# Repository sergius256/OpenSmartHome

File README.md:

# OpenSmartHome

OpenSmartHome is a hardware project aimed to develop a set of modules
capable to bind mechanical and electrical parts of house engineering
systems with known software smart house systems such as OpenHAB via
simple protocol.

# Changes

2016-05-11.

	* L298 moved to other side of the board in window-blind PCB.

	* ISP header changed to 6-pin and moved to other side of the
          PCB in window-blind.

	* Firmware for window-blind reflects changes in PCB.

2016-05-05.

	* Removed sprintf() calls to optimize memory usage.

	* Number of parser calls per rxbuffer was limited to 1 for the
          moment.

	* First version of window blind firmware written.

	* Firmware binary generated for AtMega48PA.

2016-05-02.

	* Added RS-485 shield for Raspberry Pi.

	* Added parser library to bring command recognition
          functionality to device firmwares.

	* Added window blind driver PCB layout.

	* Added PDF versions of PCB layouts and schematics for all
          hardware.

2016-04-24.

	Added window blind drive controller schematics.

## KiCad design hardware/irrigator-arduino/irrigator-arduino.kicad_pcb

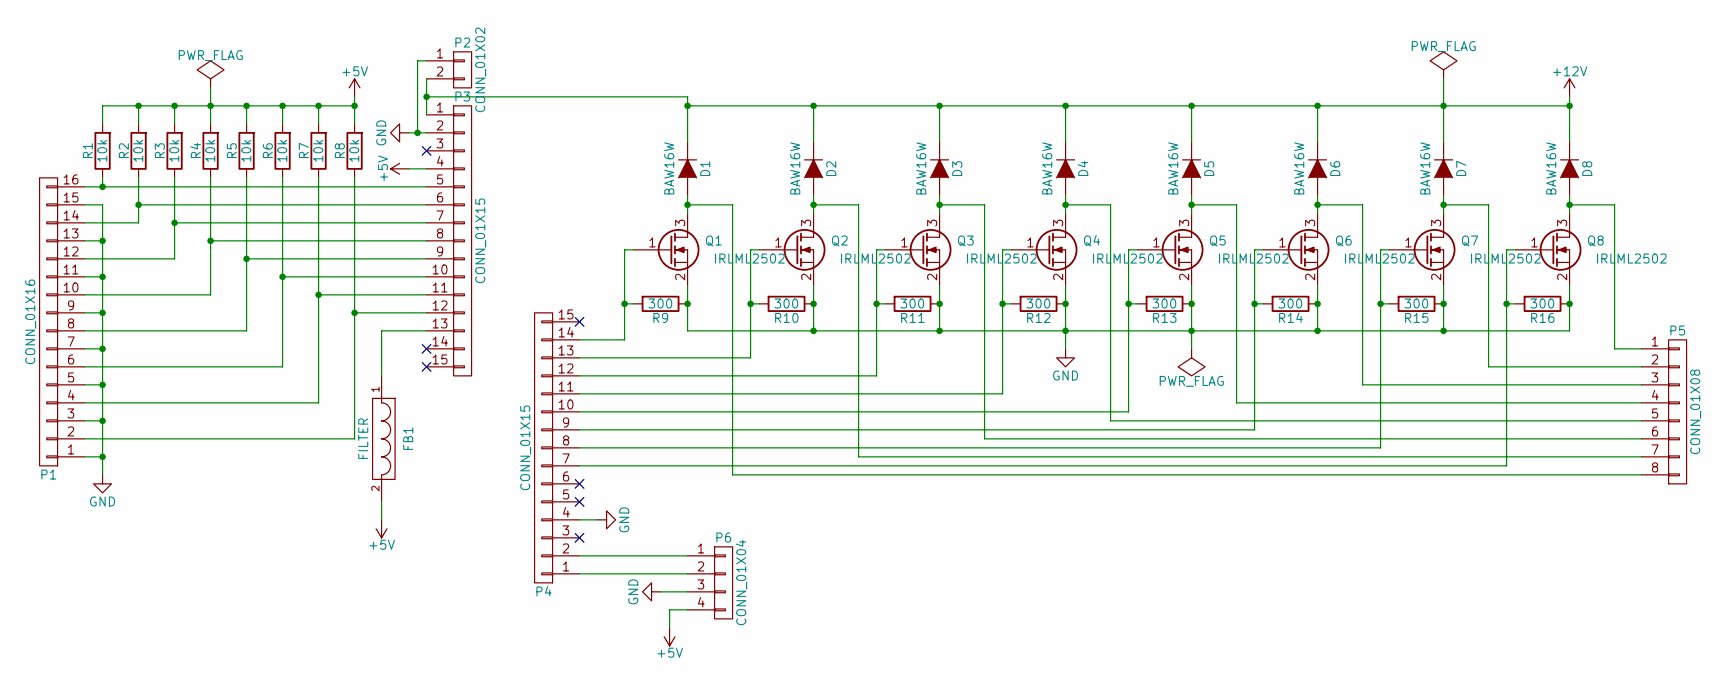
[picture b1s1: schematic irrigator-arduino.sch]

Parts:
D1, D2, D3, D4, D5, D6, D7, D8: BAW16W; D_SOD-123
FB1: FILTER; R_Axial_Power_L25.0mm_W9.0mm_P30.48mm
P1: CONN_01X16; Pin_Header_Straight_1x16_Pitch2.54mm
P2: CONN_01X02; Pin_Header_Straight_1x02_Pitch2.54mm
P3, P4: CONN_01X15; Pin_Header_Straight_1x15_Pitch2.54mm
P5: CONN_01X08; Pin_Header_Straight_1x08_Pitch2.54mm
P6: CONN_01X04; Pin_Header_Angled_1x04_Pitch2.54mm
Q1, Q2, Q3, Q4, Q5, Q6, Q7, Q8: IRLML2502; SOT-23_Handsoldering
R1, R2, R3, R4, R5, R6, R7, R8: 10k; R_1206_HandSoldering
R9, R10, R11, R12, R13, R14, R15, R16: 300; R_1206_HandSoldering

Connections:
+5V: FB1.2, P3.4, P6.4, R1.2, R2.2, R3.2, R4.2, R5.2, R6.2, R7.2, R8.2
+12V: D1.1 (K), D2.1 (K), D3.1 (K), D4.1 (K), D5.1 (K), D6.1 (K), D7.1 (K), D8.1 (K), P2.2, P3.1
GND: P1.1, P1.3, P1.5, P1.7, P1.9, P1.11, P1.13, P1.15, P2.1, P3.2, P4.4, P6.3, Q1.2 (S), Q2.2 (S), Q3.2 (S), Q4.2 (S), Q5.2 (S), Q6.2 (S), Q7.2 (S), Q8.2 (S), R9.1, R10.1, R11.1, R12.1, R13.1, R14.1, R15.1, R16.1
unnamed: D1.2 (A), P5.8, Q1.3 (D)
unnamed: D2.2 (A), P5.7, Q2.3 (D)
unnamed: D3.2 (A), P5.6, Q3.3 (D)
unnamed: D4.2 (A), P5.5, Q4.3 (D)
unnamed: D5.2 (A), P5.4, Q5.3 (D)
unnamed: D6.2 (A), P5.3, Q6.3 (D)
unnamed: D7.2 (A), P5.2, Q7.3 (D)
unnamed: D8.2 (A), P5.1, Q8.3 (D)
unnamed: FB1.1, P3.13
unnamed: P1.2, P3.12, R8.1
unnamed: P1.4, P3.11, R7.1
unnamed: P1.6, P3.10, R6.1
unnamed: P1.8, P3.9, R5.1
unnamed: P1.10, P3.8, R4.1
unnamed: P1.12, P3.7, R3.1
unnamed: P1.14, P3.6, R2.1
unnamed: P1.16, P3.5, R1.1
unnamed: P4.1, P6.2
unnamed: P4.2, P6.1
unnamed: P4.7, Q8.1 (G), R16.2
unnamed: P4.8, Q7.1 (G), R15.2
unnamed: P4.9, Q6.1 (G), R14.2
unnamed: P4.10, Q5.1 (G), R13.2
unnamed: P4.11, Q4.1 (G), R12.2
unnamed: P4.12, Q3.1 (G), R11.2
unnamed: P4.13, Q2.1 (G), R10.2
unnamed: P4.14, Q1.1 (G), R9.2

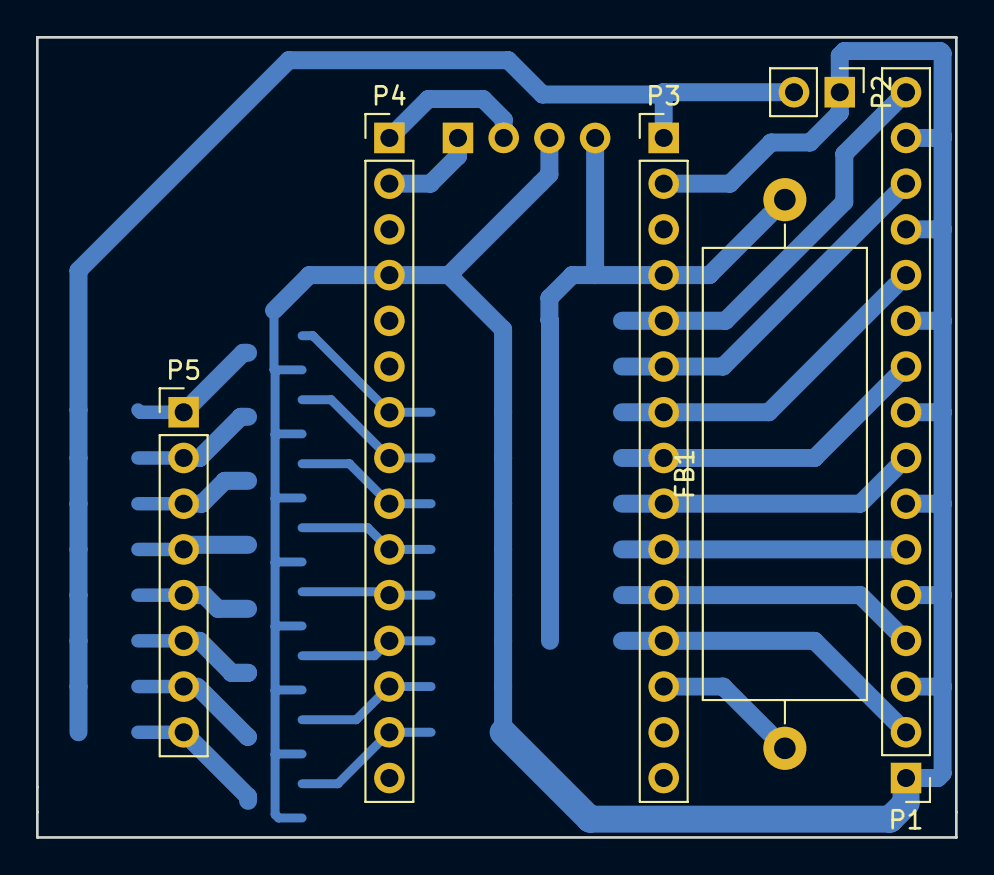
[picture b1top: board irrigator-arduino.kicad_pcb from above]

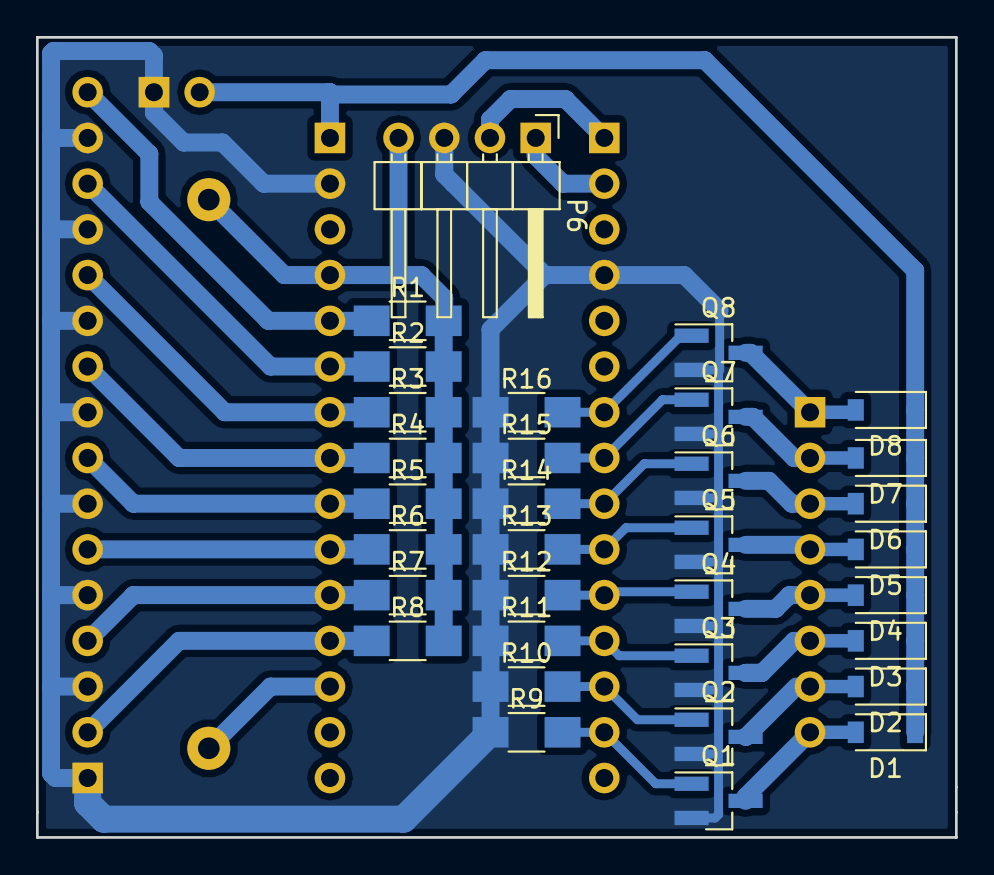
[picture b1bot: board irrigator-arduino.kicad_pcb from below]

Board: 2 copper layers, 51.1 x 44.4 mm, 39 parts (33 on the bottom side), 30 nets.

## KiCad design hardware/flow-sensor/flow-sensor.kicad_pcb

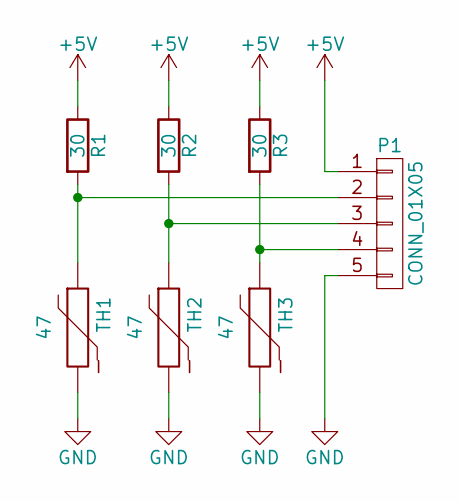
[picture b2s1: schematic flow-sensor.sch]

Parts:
P1: CONN_01X05; Pin_Header_Straight_1x05_Pitch2.54mm
R1, R2, R3: 30; R_1206_HandSoldering
TH1, TH2, TH3: 47; R_0805_HandSoldering

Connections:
+5V: P1.1, R1.1, R2.1, R3.1
GND: P1.5, TH1.2, TH2.2, TH3.2
unnamed: P1.2, R1.2, TH1.1
unnamed: P1.3, R2.2, TH2.1
unnamed: P1.4, R3.2, TH3.1

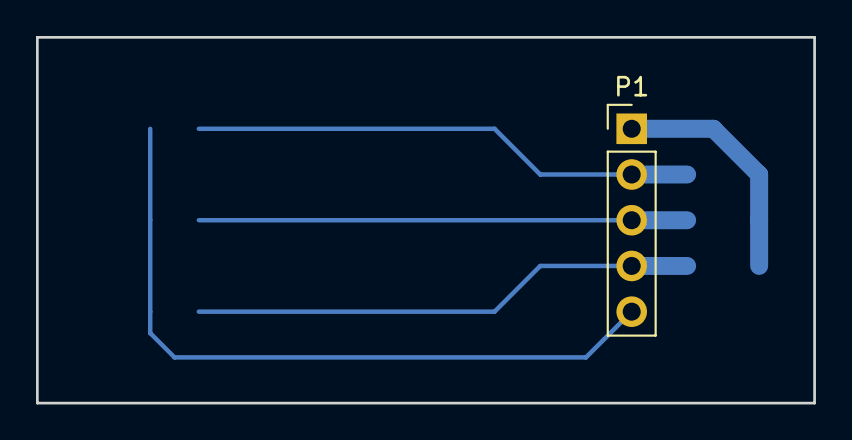
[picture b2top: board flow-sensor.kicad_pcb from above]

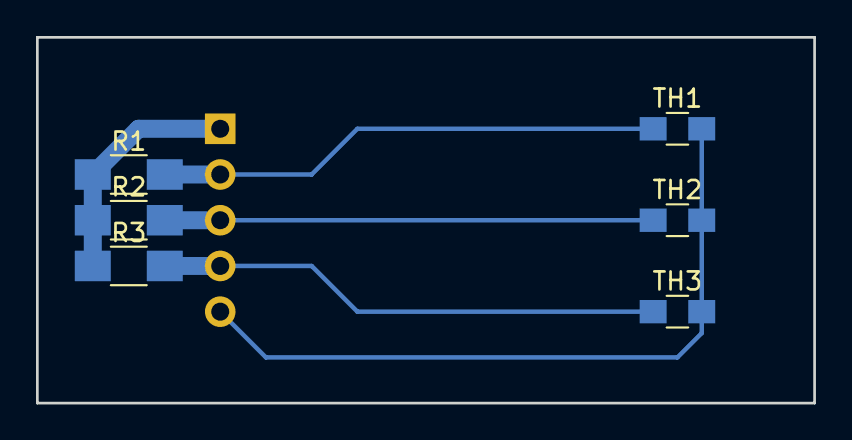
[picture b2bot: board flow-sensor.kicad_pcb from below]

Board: 2 copper layers, 43.2 x 20.3 mm, 7 parts (6 on the bottom side), 5 nets.

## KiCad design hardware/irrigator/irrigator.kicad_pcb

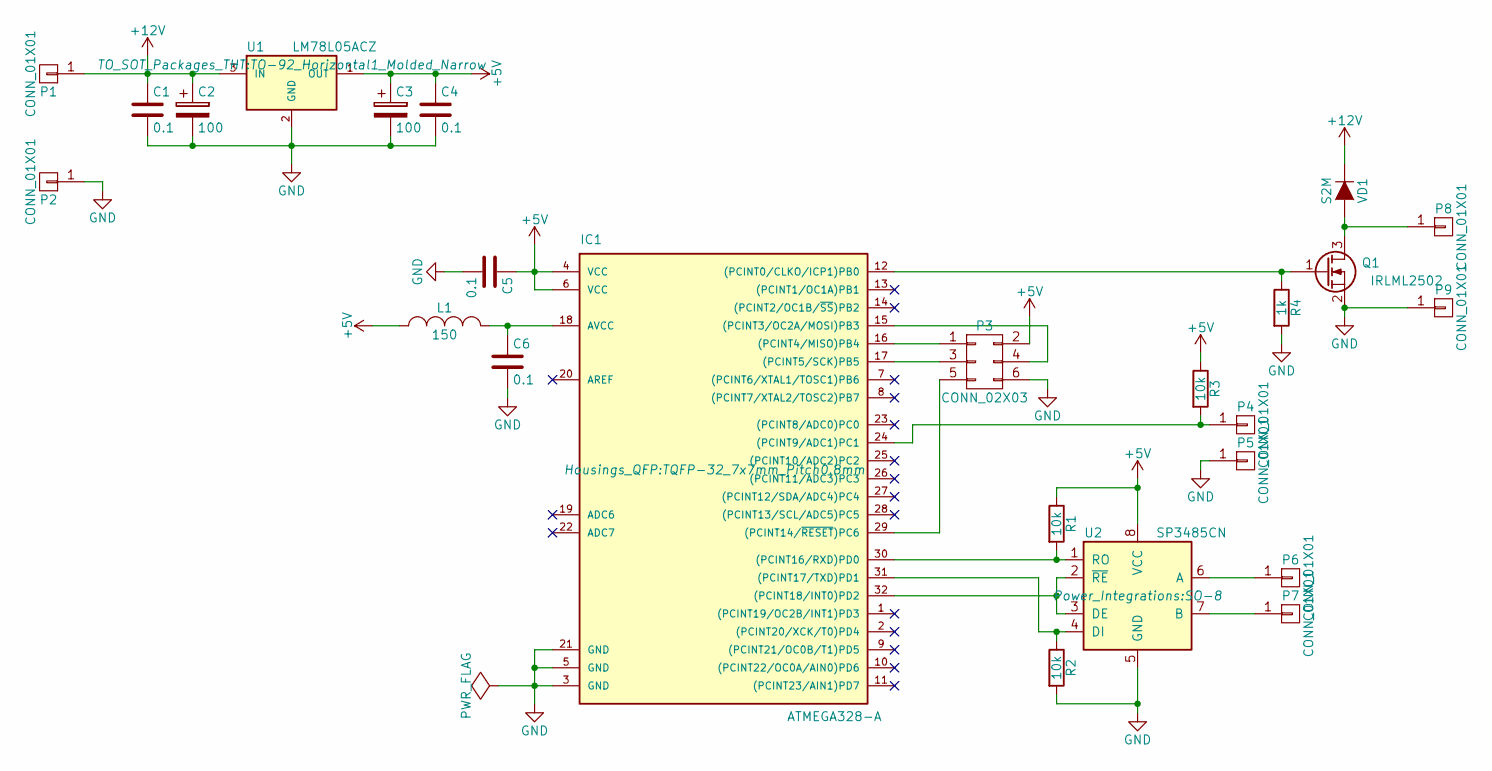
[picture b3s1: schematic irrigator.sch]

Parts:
C1, C4, C5, C6: 0.1; C_1206_HandSoldering
C2, C3: 100; TantalC_SizeD_EIA-7343_HandSoldering
IC1: ATMEGA328-A; TQFP-32_7x7mm_Pitch0.8mm
L1: 150; Choke_Horizontal_RM25mm
P1, P2, P4, P5, P6, P7, P8, P9: CONN_01X01; 1pin
P3: CONN_02X03; Pin_Header_Straight_2x03
Q1: IRLML2502; SOT-23_Handsoldering
R1, R2, R3: 10k; R_1206_HandSoldering
R4: 1k; R_1206_HandSoldering
U1: LM78L05ACZ; TO-92_Horizontal1_Molded_Narrow
U2: SP3485CN; SO-8
VD1: S2M; SMB_Handsoldering

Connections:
+5V: C3.1, C4.1, C5.1, IC1.4 (VCC), IC1.6 (VCC), L1.1, P3.2, R1.1, R3.1, U1.1 (OUT), U2.8 (VCC)
+12V: C1.1, C2.1, P1.1, U1.3 (IN), VD1.1 (K)
GND: C1.2, C2.2, C3.2, C4.2, C5.2, C6.2, IC1.3 (GND), IC1.5 (GND), IC1.21 (GND), P2.1, P3.6, P5.1, P9.1, Q1.2 (S), R2.2, R4.2, U1.2 (GND), U2.5 (GND)
unnamed: C6.1, IC1.18 (AVCC), L1.2
unnamed: IC1.12 ((PCINT0/CLKO/ICP1)PB0), Q1.1 (G), R4.1
unnamed: IC1.15 ((PCINT3/OC2A/MOSI)PB3), P3.4
unnamed: IC1.16 ((PCINT4/MISO)PB4), P3.1
unnamed: IC1.17 ((PCINT5/SCK)PB5), P3.3
unnamed: IC1.24 ((PCINT9/ADC1)PC1), P4.1, R3.2
unnamed: IC1.29 ((PCINT14/~RESET~)PC6), P3.5
unnamed: IC1.30 ((PCINT16/RXD)PD0), R1.2, U2.1 (RO)
unnamed: IC1.31 ((PCINT17/TXD)PD1), R2.1, U2.4 (DI)
unnamed: IC1.32 ((PCINT18/INT0)PD2), U2.2 (~RE~), U2.3 (DE)
unnamed: P6.1, U2.6 (A)
unnamed: P7.1, U2.7 (B)
unnamed: P8.1, Q1.3 (D), VD1.2 (A)

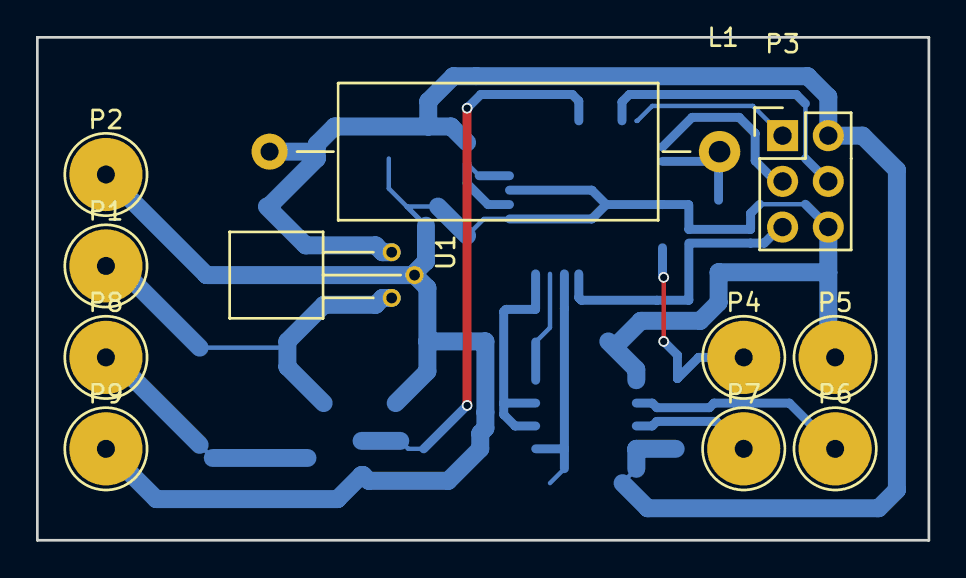
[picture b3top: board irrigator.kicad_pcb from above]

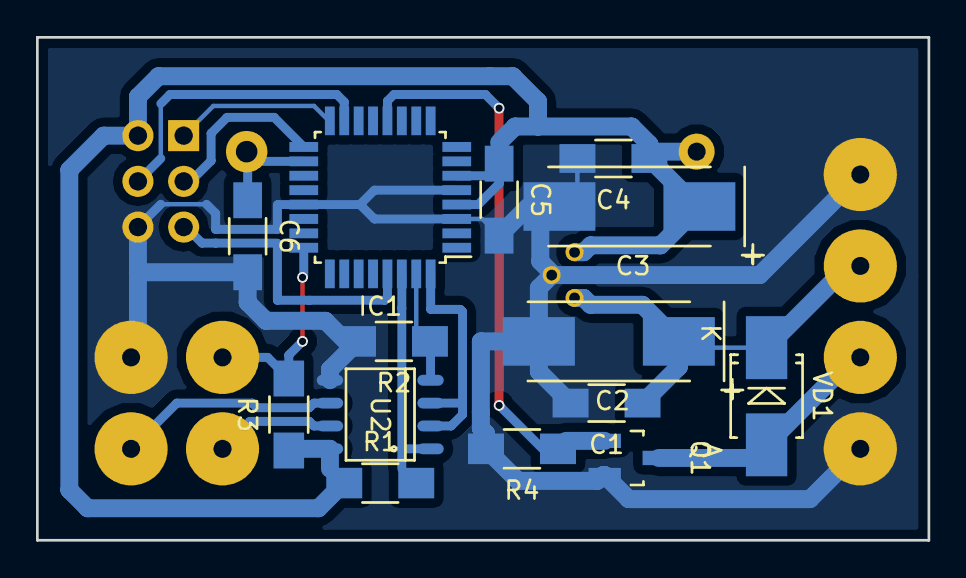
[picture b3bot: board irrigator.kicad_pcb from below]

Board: 2 copper layers, 49.5 x 27.9 mm, 25 parts (14 on the bottom side), 16 nets.

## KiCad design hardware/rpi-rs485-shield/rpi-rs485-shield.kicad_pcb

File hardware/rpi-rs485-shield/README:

OpenSmartHome RS-485 shield for Raspberry Pi copyright (C) 2016
Sergey Portnov (sergius256@gmail.com)

This schematic and printed circuit board design are released under the
terms of Creative Commons license v4.0, Attribution-ShareAlike. Author
holds no responsibility for any damage caused by the usage of this
materials.

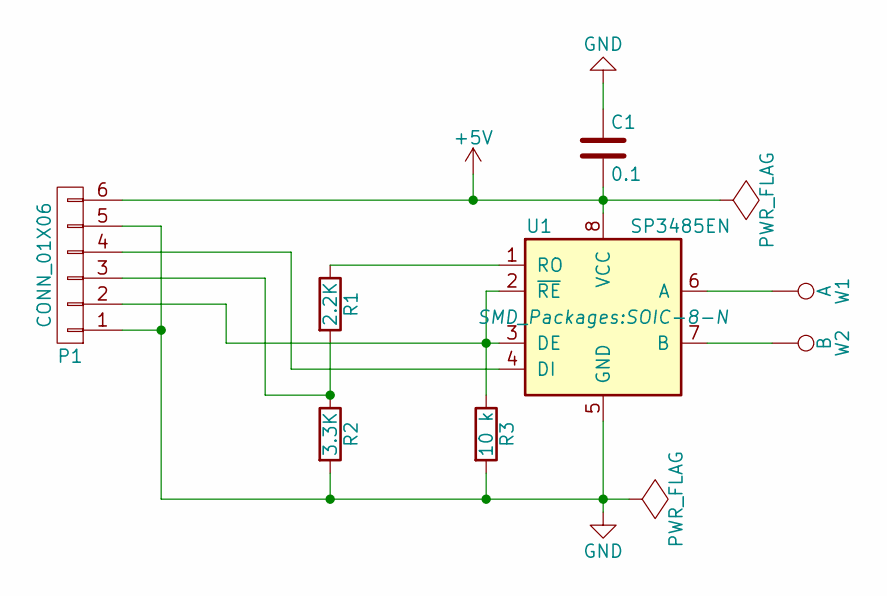
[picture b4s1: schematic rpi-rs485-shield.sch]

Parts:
C1: 0.1; C_1206_HandSoldering
P1: CONN_01X06; Pin_Header_Straight_1x06
R1: 2.2K; R_1206_HandSoldering
R2: 3.3K; R_1206_HandSoldering
R3: 10 k; R_1206_HandSoldering
U1: SP3485EN; SOIC-8-N
W1: A; SolderWirePad_single_1mmDrill
W2: B; SolderWirePad_single_1mmDrill

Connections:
+5V: C1.2, P1.6, U1.8 (VCC)
GND: C1.1, P1.1, P1.5, R2.2, R3.2, U1.5 (GND)
unnamed: P1.2, R3.1, U1.2 (~RE~), U1.3 (DE)
unnamed: P1.3, R1.2, R2.1
unnamed: P1.4, U1.4 (DI)
unnamed: R1.1, U1.1 (RO)
unnamed: U1.6 (A), W1.1
unnamed: U1.7 (B), W2.1

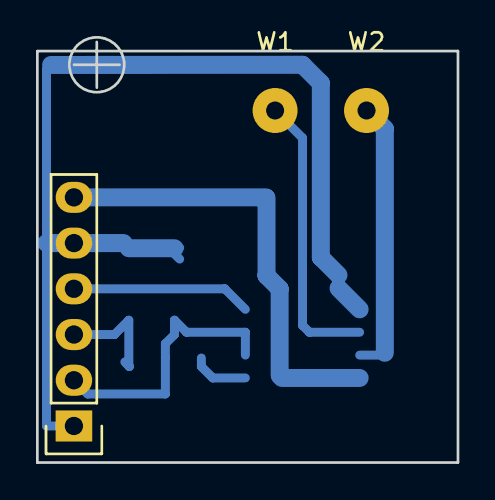
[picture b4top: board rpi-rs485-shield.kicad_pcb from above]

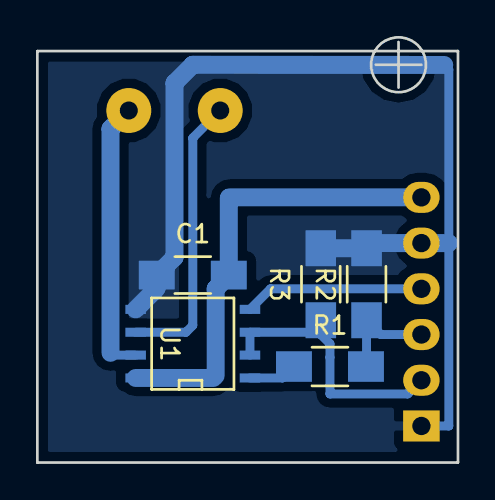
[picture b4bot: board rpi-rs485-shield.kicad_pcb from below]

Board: 2 copper layers, 23.4 x 23.6 mm, 8 parts (5 on the bottom side), 8 nets.

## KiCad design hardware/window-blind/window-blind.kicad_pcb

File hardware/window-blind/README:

OpenSmartHome window blind drive copyright (C) 2014-2016
Sergey Portnov (sergius256@gmail.com),
Raed Romanov (raid_r@mail.ru),
Anatoly Karavaev (karavaevas@gmail.com),
Evgeny Kaner (kanerea@xakep.ru)

This schematic and printed circuit board design are released under the
terms of Creative Commons license v4.0, Attribution-ShareAlike.

Schematics use Kicad Library by W. Lain - kcswalter@member.fsf.org.

Authors holds no responsibility for any damage caused by the usage of
this materials.

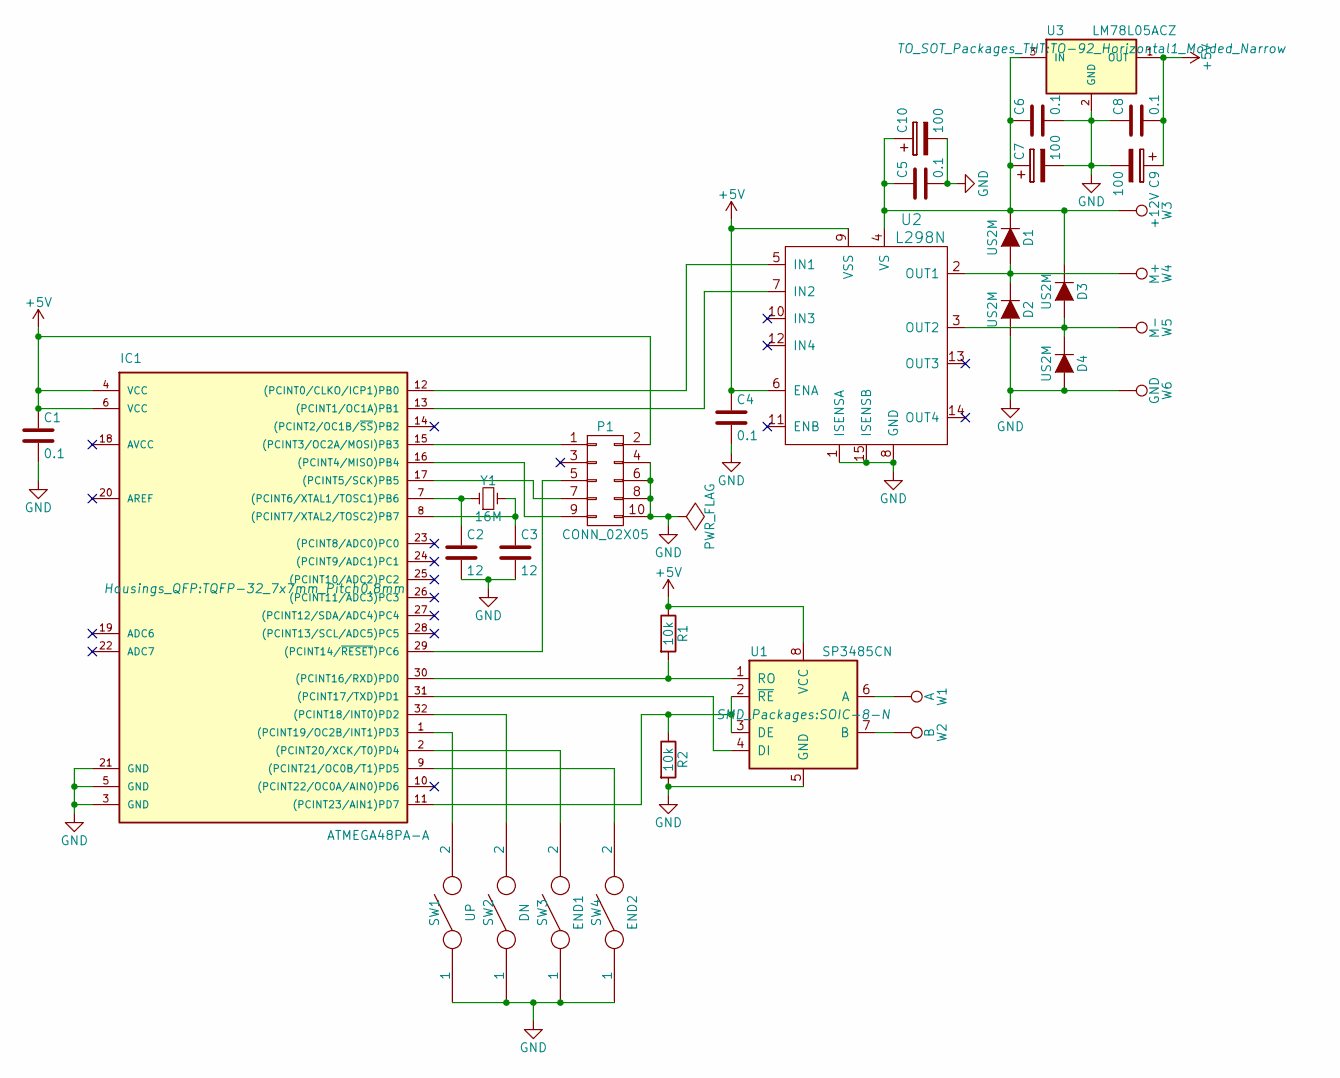
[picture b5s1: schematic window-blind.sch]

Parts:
C1, C4, C5, C6, C8: 0.1; C_1206_HandSoldering
C2, C3: 12; C_1206_HandSoldering
C7, C9, C10: 100; TantalC_SizeD_EIA-7343_HandSoldering
D1, D2, D3, D4: US2M; DO-214AB_Handsoldering
IC1: ATMEGA48PA-A; TQFP-32_7x7mm_Pitch0.8mm
P1: CONN_02X05; Pin_Header_Straight_2x05
R1, R2: 10k; R_1206_HandSoldering
SW1: UP; SW_SPST_B3S-1000
SW2: DN; SW_SPST_B3S-1000
SW3: END1; Resistor_Horizontal_RM15mm
SW4: END2; Resistor_Horizontal_RM15mm
U1: SP3485CN; SOIC-8-N
U2: L298N; Multiwatt_15_Vertical
U3: LM78L05ACZ; TO-92_Horizontal1_Molded_Narrow
W1: A; SolderWirePad_single_1mmDrill
W2: B; SolderWirePad_single_1mmDrill
W3: +12V; SolderWirePad_single_1mmDrill
W4: M+; SolderWirePad_single_1mmDrill
W5: M-; SolderWirePad_single_1mmDrill
W6: GND; SolderWirePad_single_1mmDrill
Y1: 16M; Crystal_HC49-SD_SMD

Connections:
+5V: C1.1, C4.1, C8.2, C9.1, IC1.4 (VCC), IC1.6 (VCC), P1.2, R1.1, U1.8 (VCC), U2.6 (ENA), U2.9 (VSS), U3.1 (OUT)
GND: C1.2, C2.2, C3.2, C4.2, C5.2, C6.2, C7.2, C8.1, C9.2, C10.2, D2.2 (A), D4.2 (A), IC1.3 (GND), IC1.5 (GND), IC1.21 (GND), P1.4, P1.6, P1.8, P1.10, R2.2, SW1.1, SW2.1, SW3.1, SW4.1, U1.5 (GND), U2.1 (ISENSA), U2.8 (GND), U2.15 (ISENSB), U3.2 (GND), W6.1
unnamed: C2.1, IC1.7 ((PCINT6/XTAL1/TOSC1)PB6), Y1.1
unnamed: C3.1, IC1.8 ((PCINT7/XTAL2/TOSC2)PB7), Y1.2
unnamed: C5.1, C6.1, C7.1, C10.1, D1.1 (K), D3.1 (K), U2.4 (VS), U3.3 (IN), W3.1
unnamed: D1.2 (A), D2.1 (K), U2.2 (OUT1), W4.1
unnamed: D3.2 (A), D4.1 (K), U2.3 (OUT2), W5.1
unnamed: IC1.1 ((PCINT19/OC2B/INT1)PD3), SW1.2
unnamed: IC1.2 ((PCINT20/XCK/T0)PD4), SW3.2
unnamed: IC1.9 ((PCINT21/OC0B/T1)PD5), SW4.2
unnamed: IC1.11 ((PCINT23/AIN1)PD7), R2.1, U1.2 (~RE~), U1.3 (DE)
unnamed: IC1.12 ((PCINT0/CLKO/ICP1)PB0), U2.5 (IN1)
unnamed: IC1.13 ((PCINT1/OC1A)PB1), U2.7 (IN2)
unnamed: IC1.15 ((PCINT3/OC2A/MOSI)PB3), P1.1
unnamed: IC1.16 ((PCINT4/MISO)PB4), P1.9
unnamed: IC1.17 ((PCINT5/SCK)PB5), P1.7
unnamed: IC1.29 ((PCINT14/~RESET~)PC6), P1.5
unnamed: IC1.30 ((PCINT16/RXD)PD0), R1.2, U1.1 (RO)
unnamed: IC1.31 ((PCINT17/TXD)PD1), U1.4 (DI)
unnamed: IC1.32 ((PCINT18/INT0)PD2), SW2.2
unnamed: U1.6 (A), W1.1
unnamed: U1.7 (B), W2.1

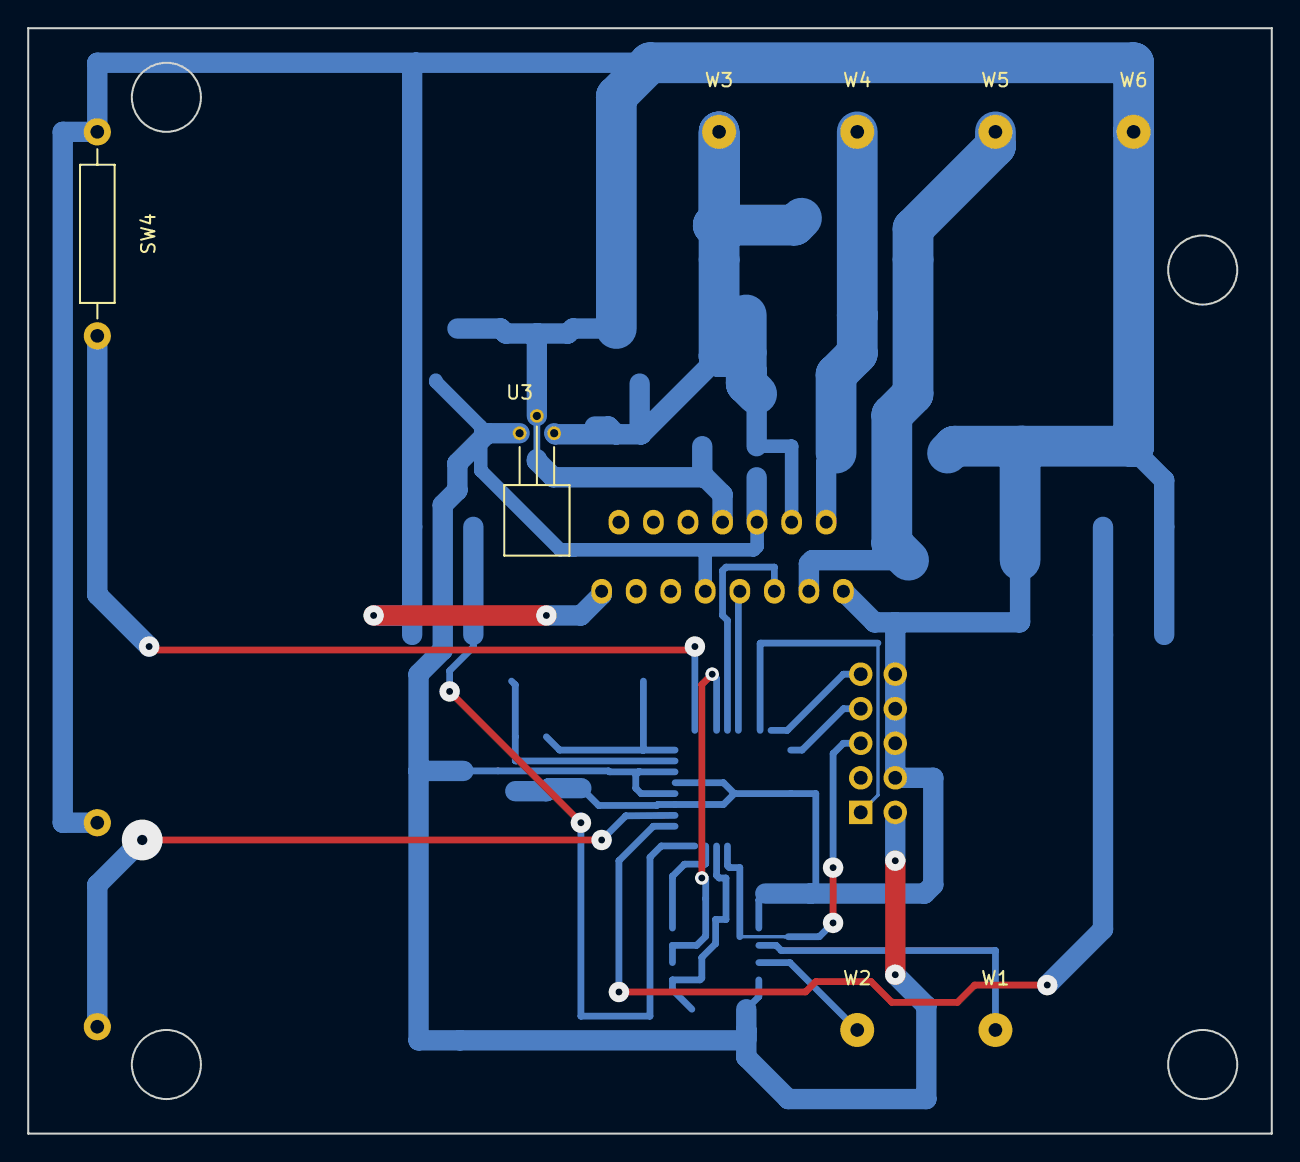
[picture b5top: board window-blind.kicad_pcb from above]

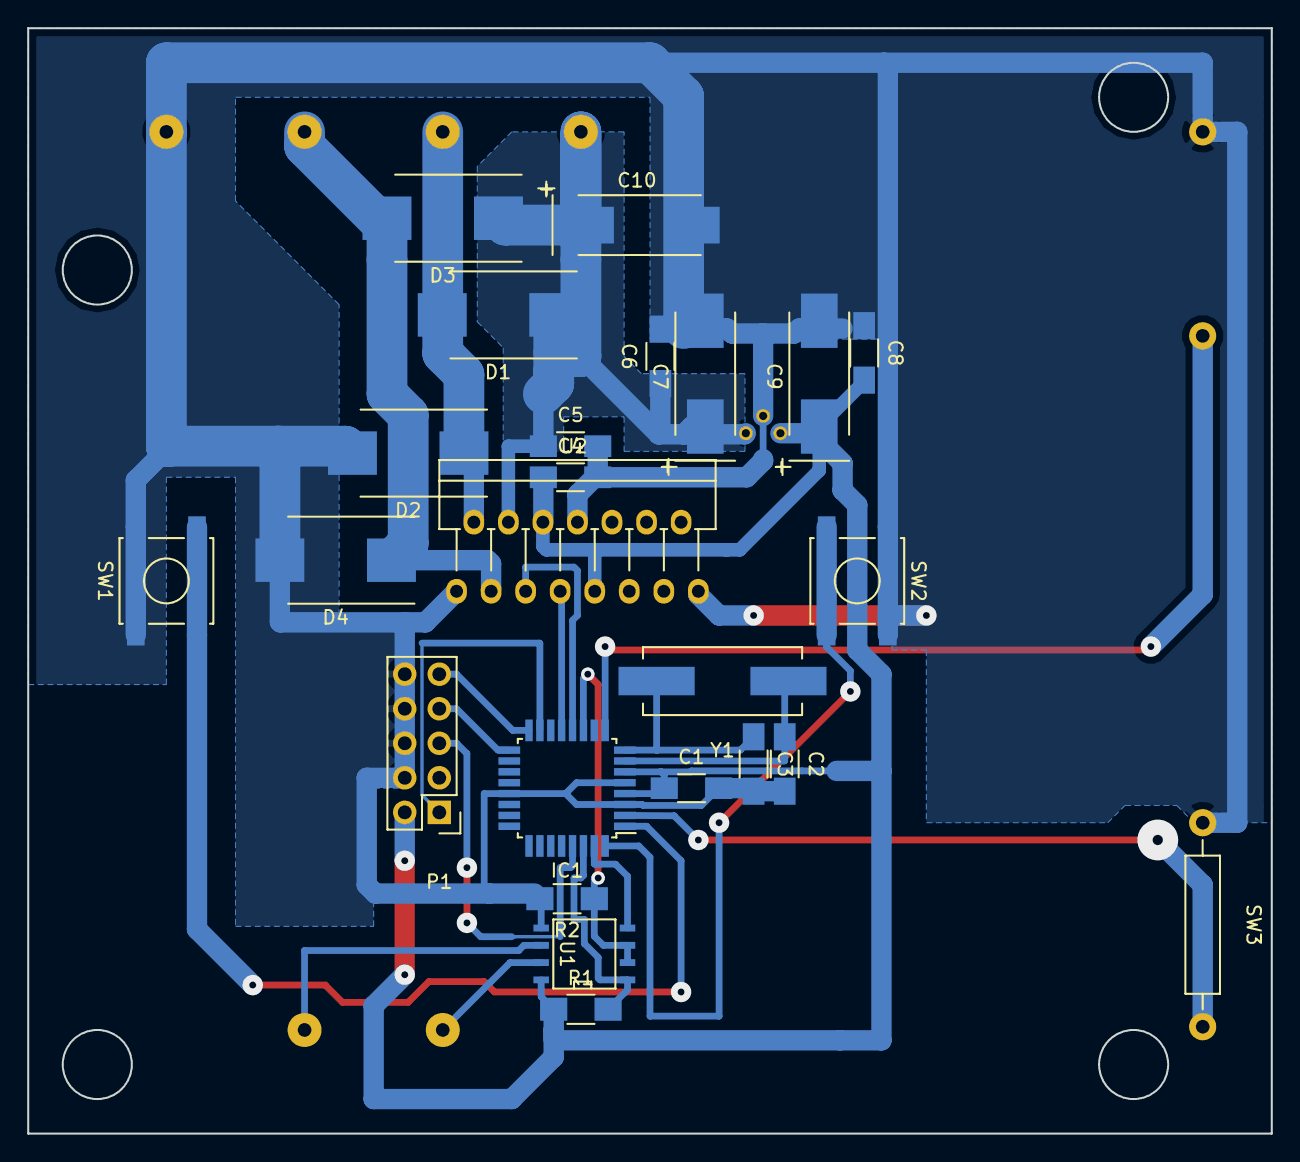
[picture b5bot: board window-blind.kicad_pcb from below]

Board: 2 copper layers, 91.4 x 81.3 mm, 32 parts (24 on the bottom side), 22 nets.

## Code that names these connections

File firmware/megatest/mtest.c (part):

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
// UART initialization function.
void uart_init(void) {
  set_output(DDRD, PD7);  // PD7 pin is connected to RE/DE pins of MAX485
  output_low(PORTD, PD7); // It should be set to 0 until we really transmitting someting out

  UBRR0H = UBRRH_VALUE;
  UBRR0L = UBRRL_VALUE;
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// Function that transmits txbuffer through UART
void uart_transmit(void) {
  unsigned char i=0;
  // Here we need to put PD7 pin to 1 to turn MAX485 into transmitter mode
  output_high(PORTD, PD7);
  // The transmission itself
  do {
    while // Wait for empty transmit buffer
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    i++;
  } while(txbuffer[i-1]!='\n');
  // Making all things back
  output_low(PORTD, PD7);
}

// Recieving function is an interrupt handler
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       */
    case 0: // Initialize system
      uart_init();
      set_output(DDRB, PB0);  // PB0 pin is connected to L298 IN1
      set_output(DDRB, PB1);  // PB1 pin is connected to L298 IN2
      
      DDRD=0b10000011;
      
      /*      set_input(DDRD, PD2); // DOWN button
      set_input(DDRD, PD3); // UP button
      set_input(DDRD, PD4); // END1 contact
      set_input(DDRD, PD5); // END2 contact */
      PORTD |= 0b00111100;  // Switching pull-up resistors on

      output_high(PORTB, PB0);
      output_low(PORTB, PB1); // Switching motor on in forward direction
      

      output_low(PORTB, PB0);
      output_high(PORTB, PB1); // Switching motor on in backward direction


      output_low(PORTB, PB0);
      output_low(PORTB, PB1); // Switching motor off
      
      // now MovementTimeCurrent contains number of 10 ms time cycles
      // from current posisiton to upper and MovementTimeFull contains
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      if(((PIND & 0b0100) == 0) || ((PIND & 0b1000) == 0))// DOWN or UP button pressed
	ProtectiveCounter++;
      _delay_ms(20);
      if((ProtectiveCounter>2) && ((PIND & 1<<PD2) == 0)) { // DOWN button still pressed
	DesiredPosition=0;
      }
      if((ProtectiveCounter>2) && ((PIND & 1<<PD3) == 0)) { // DOWN button still pressed
	DesiredPosition=100;
      }
      // Now let's check our command buffer
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	way to stop this is pressing any button.
       */
    case 2: // Moving up
      output_high(PORTB, PB0);
      output_low(PORTB, PB1); // Switching motor on in forward direction

      for(ProtectiveCounter=0;ProtectiveCounter<2;MovementTimeCurrent--) {
	_delay_ms(10);
	if(((PIND & 1<<PD4) == 0) || ((PIND & 1<<PD2) == 0) || ((PIND & 1<<PD3) == 0))
	  ProtectiveCounter++;
	if(CurrentPosition == DesiredPosition || MovementTimeCurrent <= 0)
	  break;
	CurrentPosition=(int)MovementTimeCurrent/MovementTimeFull*100;
      }

      output_low(PORTB, PB0);
      output_low(PORTB, PB1); // Switching motor off
      DesiredPosition=CurrentPosition;
      ProtectiveCounter=0;
      if(ReportOkFlag)
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	only way to stop this is pressing any button.
       */
    case 3: // Moving down
      output_low(PORTB, PB0);
      output_high(PORTB, PB1); // Switching motor on in backward direction

      
      for(ProtectiveCounter=0;ProtectiveCounter<2;MovementTimeCurrent++) {
	_delay_ms(10);
	if(((PIND & 1<<PD5) == 0) || ((PIND & 1<<PD2) == 0) || ((PIND & 1<<PD3) == 0))
	  ProtectiveCounter++;
	if(CurrentPosition == DesiredPosition || MovementTimeCurrent >= MovementTimeFull)
	  break;
	CurrentPosition=(int)MovementTimeCurrent/MovementTimeFull*100;
      }

      output_low(PORTB, PB0);
      output_low(PORTB, PB1); // Switching motor off
      DesiredPosition=CurrentPosition;
      ProtectiveCounter=0;
      if(ReportOkFlag)
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
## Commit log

2016-04-24 Adding initial files.
2016-04-25 Built sunblind PCB layout
2016-04-25 Updated window blind driver PCB to ver. 1.0
2016-04-25 Added files via upload
2016-04-25 Slightly rebuilt PCB, added some functions to use in firmware
2016-04-25 Updated SVG and PDF files
2016-04-26 Moved filter capacitors on PCB, rebuilt SVG.
2016-05-01 Parser was written to interpret incoming commands.
2016-05-02 Changes from 2016-05-02
2016-05-02 2016-05-02: fixes in functions.c
2016-05-05 2016-05-05 daytime
2016-05-07 2016-05-07: removed sscanf() calls
2016-05-11 Changes from 2016-05-11
2016-05-12 Reformatted code, cleaned up filesystem
2016-05-12 UART functions moved to a separate file
2016-05-16 Corrected number of pin conected to MAX485
2016-05-19 Changes from 2016-05-19
2017-09-28 Added Arduino-based versions of irrigator and window blind.
2017-09-28 Debug commit.
2017-09-28 Added irrigator-arduino firmware.
2017-10-03 Correcter irrigator firmware code.

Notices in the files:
firmware/megatest/mtest.c:
Copyright © 2016 Sergey Portnov, Eugeny Kaner
This program is free software: you can redistribute it and/or modify
it under the terms of the GNU General Public License as published by
the Free Software Foundation, either version 3 of the License, or
(at your option) any later version.
hardware/rpi-rs485-shield/rpi-rs485-shield.kicad_pcb:
CC-BY-SA 4.0
hardware/window-blind/window-blind.kicad_pcb:
License: CC-BY-SA 4.0
